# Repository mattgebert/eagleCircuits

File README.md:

# eagleCircuits
Custom Designed Circuits constructed in Eagle for various purposes.

## 1. [Differential Amplifier x2](https://github.com/mattgebert/eagleCircuits/tree/master/BEC%20FPGA-ADC%20Differential%20Amplifier)
A two unit differential amplifier designed to run for the ADA4807-2 Module.
Used in a BEC lab to step down a ADC signal centred around 1V (0V to 2V) down 
to a 0V bias (-5V to 5V). 

## 2. [Probe Station Board](https://github.com/mattgebert/eagleCircuits/tree/master/ProbeStationBoard)
A general board to load 1cm x 1cm electronic samples on. Provides pads to create electrical connections without damaging sample.
Provides 10x unconnected pads (3.18mm^2). Also provides 1x sample pad (7.8mm^2) & 2x gate pads (4.13mm^2) connected, to load the substrate base and connect probes to respectively.

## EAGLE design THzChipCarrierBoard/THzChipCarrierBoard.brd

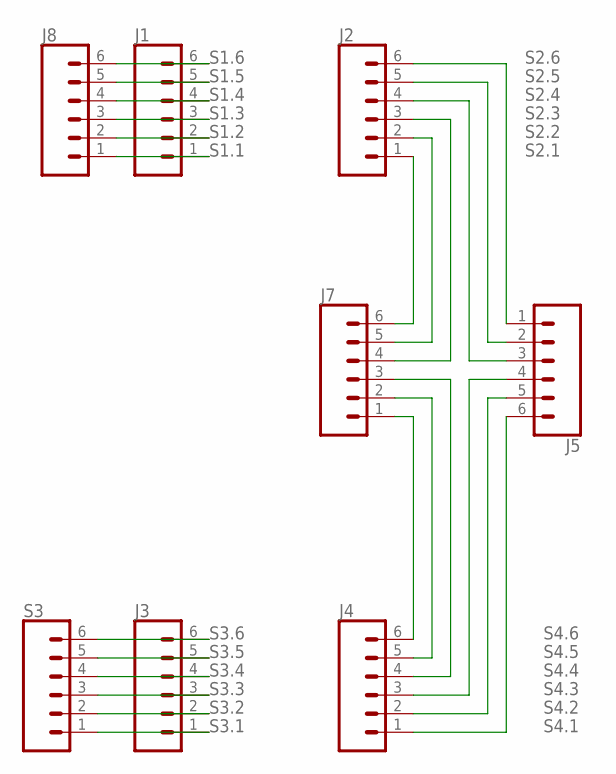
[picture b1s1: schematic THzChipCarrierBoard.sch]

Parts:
J1, J2, J3, J4, J5, J7, J8: CONN_06SILK_FEMALE_PTH; 1X06
S3: CONN_06SILK_FEMALE_PTH; 1X06

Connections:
S1.1: J1.1, J8.1
S1.2: J1.2, J8.2
S1.3: J1.3, J8.3
S1.4: J1.4, J8.4
S1.5: J1.5, J8.5
S1.6: J1.6, J8.6
S2.1: J2.1, J7.6
S2.2: J2.2, J7.5
S2.3: J2.3, J7.4
S2.4: J2.4, J5.3
S2.5: J2.5, J5.2
S2.6: J2.6, J5.1
S3.1: J3.1, S3.1
S3.2: J3.2, S3.2
S3.3: J3.3, S3.3
S3.4: J3.4, S3.4
S3.5: J3.5, S3.5
S3.6: J3.6, S3.6
S4.1: J4.1, J5.6
S4.2: J4.2, J5.5
S4.3: J4.3, J5.4
S4.4: J4.4, J7.3
S4.5: J4.5, J7.2
S4.6: J4.6, J7.1

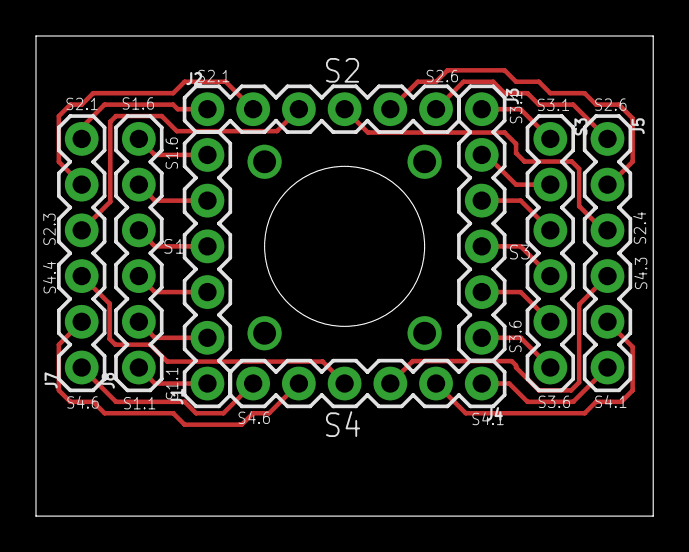
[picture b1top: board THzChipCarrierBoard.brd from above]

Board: 2 copper layers, 34.3 x 26.7 mm, 8 parts (0 on the bottom side), 24 nets.

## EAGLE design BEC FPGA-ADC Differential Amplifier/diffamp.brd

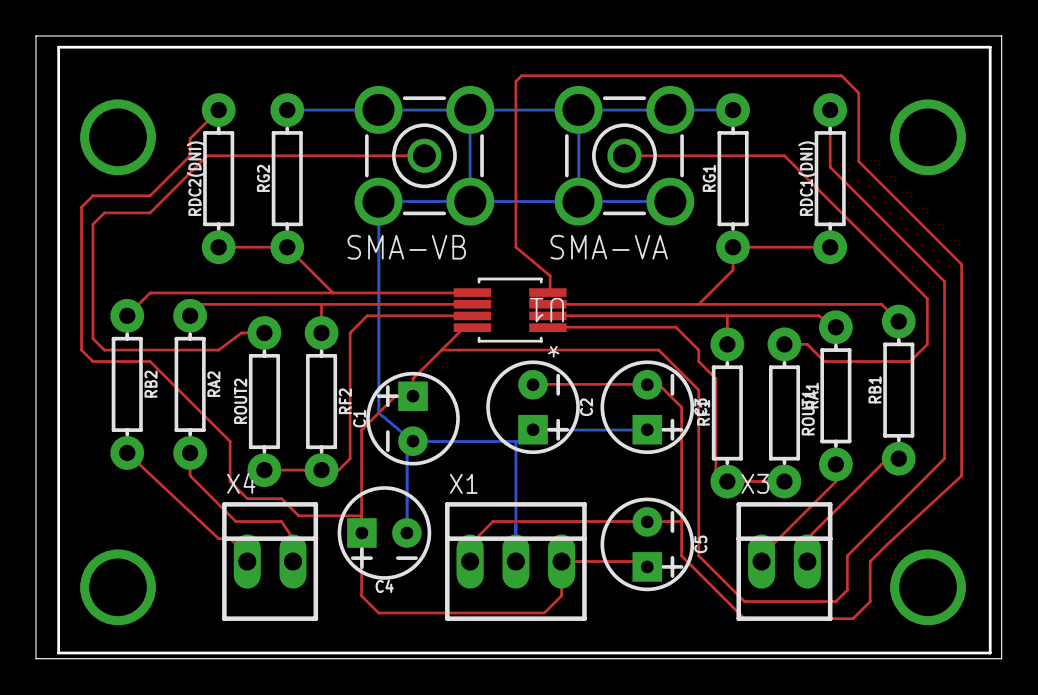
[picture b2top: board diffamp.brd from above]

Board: 2 copper layers, 53.5 x 34.4 mm, 23 parts (0 on the bottom side), 15 nets.

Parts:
C1, C2: 10uF; CPOL-RADIAL-2.5MM-5MM
C3, C4: 0.1uF; CPOL-RADIAL-2.5MM-5MM
C5: 10nF; CPOL-RADIAL-2.5MM-5MM
RA1, RA2: 500; AXIAL-0.3
RB1, RB2: 500; AXIAL-0.3
RDC1(DNI), RDC2(DNI): 1k; AXIAL-0.3
RF1, RF2: 1k; AXIAL-0.3
RG1, RG2: 1k; AXIAL-0.3
ROUT1, ROUT2: 0; AXIAL-0.3
SMA-VA: BU-SMA-V
SMA-VB: BU-SMA-V
U1: ADA4807-2ARMZRM_8-M; RM_8-M
X1: 22-23-2031
X3, X4: 22-23-2021

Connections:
+5V: C1.1, C4.1, C5.1, RDC1(DNI).P$2, RDC2(DNI).P$2, U1.8, X1.3
+IN1: RB1.P$2, RDC1(DNI).P$1, RG1.P$1, U1.3
+IN2: RB2.P$1, RDC2(DNI).P$1, RG2.P$1, U1.5
-5V: C2.2, C3.2, C5.2, U1.4, X1.1
-IN1: RA1.P$2, RF1.P$2, U1.2
-IN2: RA2.P$1, RF2.P$1, U1.6
DAC-A1: RA1.P$1, X3.1
DAC-A2: RB1.P$1, X3.2
DAC-B1: RA2.P$2, X4.2
DAC-B2: RB2.P$2, X4.1
GND: C1.2, C2.1, C3.1, C4.2, RG1.P$2, RG2.P$2, SMA-VA.2, SMA-VA.3, SMA-VA.4, SMA-VA.5, SMA-VB.2, SMA-VB.3, SMA-VB.4, SMA-VB.5, X1.2
VOUT1: RF1.P$1, ROUT1.P$2, U1.1
VOUT2: RF2.P$2, ROUT2.P$1, U1.7
VSMA1: ROUT1.P$1, SMA-VA.1
VSMA2: ROUT2.P$2, SMA-VB.1

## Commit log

2017-09-05 Initial commit for circuit repositories.
2017-09-09 Generated proper shematic and updated board components for Diff Amplifier. Holes added properly, acces with Vias for supply and ground voltages.
2017-09-14 Updated differential amplifier circuit. About to begin rewiring. Also removing extra connectors, single port access and that's all.
2017-09-14 Added new source capacitors.
2017-09-14 Added output series resistance. Not Routed
2017-09-14 Added ground plane and zero ohm resistors. Board Layout modified.
2017-09-14 Re-routed wires to leave more spacing on PCB.
2017-09-15 Cloned diff amp, to create new circuit that is more optimised in layout and will behave nicer.
2017-09-17 Secondary Design, for optimised tracks and space.
2017-09-17 Updated new design, added copper pour for groundplate.
2017-09-17 Updated Silkscreen text, generated gerbers and sent for print.
2017-09-17 Create README.md
    Added first differential amplifier description entry.
2017-09-17 Forgot to process drd/txt file for holes.
2017-09-17 Updated description
2018-07-17 Started project for Probe Station Boards
    Probe station boards are used to mount small 1cm x 1cm samples on. Designed pads to be connected to a sample, for interfacing with probes.
2018-07-18 Finished design for Probe Station Board, added gerbers and library pad files.
2018-07-18 Used pcbway's converter for .brd files to generate gerbers.
    With updates of Eagle 9.X the gerber files generated no longer work with pcbway's interface. Used their own in house converters to generate PCB design files.
2018-07-20 Small edits to viewing PCBs
2020-01-08 Added new THz board circuit
2020-01-09 Updated ChipCarrier board design, added copper plate backing, soldermasks and what not
2021-01-11 Added design for probe station breakout box
2021-01-11 Added make-before-break switches to schematic
2021-01-20 Added banana connectors to breakout box circuit

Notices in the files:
parts and their libraries:
SparkFun-Capacitors: Licensing: Creative Commons ShareAlike 4.0 International - https://creativecommons.org/licenses/by-sa/4.0
